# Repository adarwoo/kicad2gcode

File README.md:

# kicad2gcode

This project aims at providing a highly customisable tool to generate some GCode
for any CNC directly from a KiCAD PCB file.
It aims to be used in 3 different ways:
1. As a KiCAD plugin, so the GCode can be produced right from KiCAD
2. As a standalone command line type application for automation into other processed
3. As an API to use in a more integrated solution such as a Rasperry Pi connected to the CNC

**NOTE**: THIS IS WORK IN PROGRESS. It is activelly being developped but is not completed.

## Features

### Support for ATC and manual tool change
Define standard racks and use them.
The existing rack is evaluated and an updated version is generated along with
instructions for the changes required (add or replace a bit).

Racks are optimized to minimise the number of tool changes and are always sorted
to make the operator's life easier.
Racks can have un-usable slots too.

Get rack composition clearly layed out for you.

### Custom shop tools
Define you cutting tools on hand and let the software work it out for you.
It uses your tolerance to optimise the work.
If holes cannot be drilled (no adequate size), a router bit is used instead.
The software check the drilling depth required based on the bit diameter and
geometry and ensure it does not go through the backing board.

### Optimized machining
A Travelling Salesman Problem is applied throughout to minimise traveling time.
This is applied for drilling and routing.

### Support for different units
Versed in all unit systems, you can use the unit you prefer. This can be
used throughout the configuration. The units used are kept throughout.
Imperial can also be expressed in fractions, with the fractions kept in the display.

### Manufacturer's data
The configuration comes with manufacturing data to optimize the experience for
each cutting tool.
The software can extrapolate the manufacturing data for in-between sizes.
The generated code optimised the feed rate and spindle speed based on the
manufacturing data and the CNC capability.

## Installation
The intent is to host it on pip -that's outstanding too.
```bash
$ pip install kicad2gcode
```

## Usage

```
Usage: kicad2gcode [OPTIONS] FILENAME

  A utility which take a KiCAD v7 PCB and creates the GCode for a CNC to drill
  and route the PCB. The utility is heavily configurable. The initial set of
  configuration files is create the first time the utility runs. You can then
  edit them. The default path is ~/.kicad2gcode.

Options:
  -p, --pth              Drill and route all requiring plating.
  -n, --npth             Final drills and route and non-plated features
  -l, --outline          Route the PCB outiline
  -a, --all              Do all operations
  -o, --output FILENAME  Specify an output file name. Defaults to stdout
  --help                 Show this message and exit.
```

## Contributing

My objective is to get a working application by September 2024. This should machine
holes and outlines (pth and npth).
The outiline routing is turning out far more complex than I had anticipated, since
the output data from KiCAD are dijointed segments, requiring to re-create a closed
geometry using Eulerian Path and other graph theory. As KiCAD supports non-linear
geometry, this is made even hardware, and require some approximation.
I am using the work from https://github.com/kicad2gcode/kicad2gcode (which relies on Gerber
data) for inspiration - both making it Pythonic.
The effort is also helping the project move towards being able to engrave PCBs and
promoting an architecture which should allow for engraving. But I have no need
for engraving for now as I etch PCBs.
Let me know if you are interrested in contributing.
The tests do not provide 100% coverage yet and the code could be cleaned up too.

## License

`kicad2gcode` was created by Guillaume ARRECKX.
It is licensed under the terms of the GNU General Public License v3.0 license.

## Credits

`kicad2gcode` was created with [`cookiecutter`](https://cookiecutter.readthedocs.io/en/latest/) and the `py-pkgs-cookiecutter` [template](https://github.com/py-pkgs/py-pkgs-cookiecutter).

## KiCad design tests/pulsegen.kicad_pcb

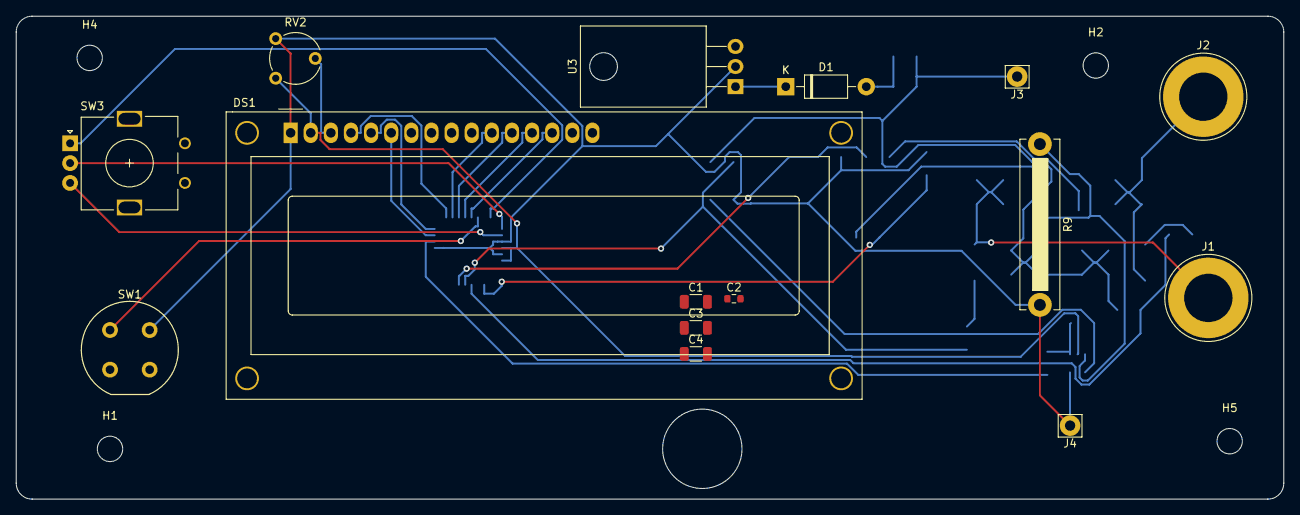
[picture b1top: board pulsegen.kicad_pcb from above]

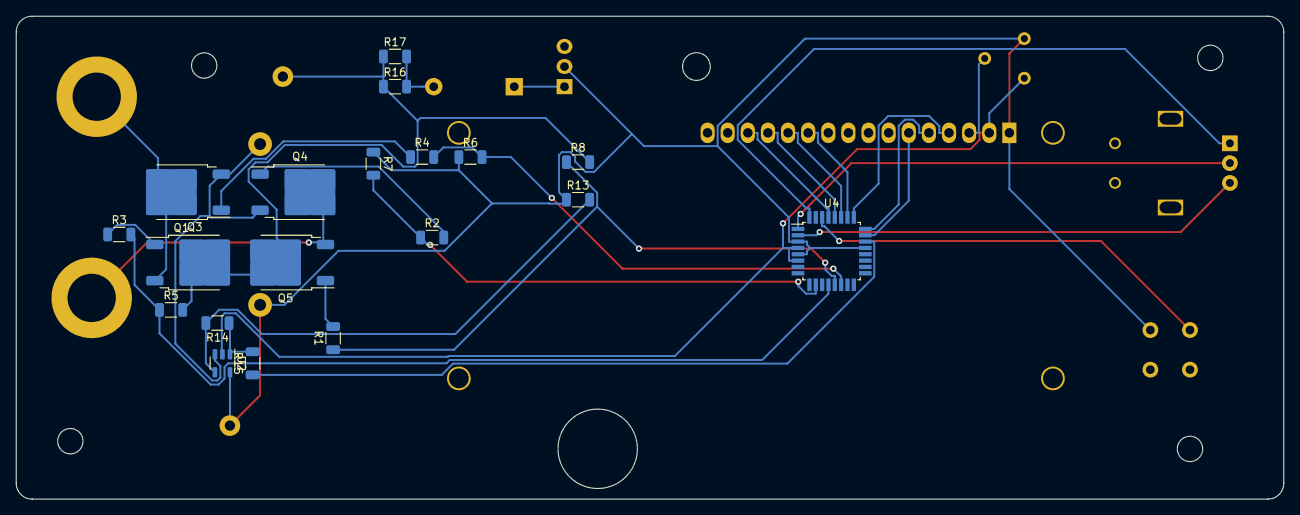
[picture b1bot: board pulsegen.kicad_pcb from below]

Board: 2 copper layers, 160.0 x 61.0 mm, 38 parts (19 on the bottom side), 32 nets.

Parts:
C1, C3, C4: 10u; R_1206_3216Metric
C2: C; R_0603_1608Metric
D1: 1N4007; D_DO-41_SOD81_P10.16mm_Horizontal
DS1: WC1602A
H1, H2, H4, H5: MountingHole; MountingHole_3.2mm_M3
J1, J2: Screw_Terminal_01x01; Banana_Jack_1Pin
J3, J4: Screw_Terminal_01x01; Pin_D1.3mm_L11.3mm_W2.8mm_Flat
Q1, Q4: QM6006D; TO-252-2
Q3, Q5: QM6015D; TO-252-2
R1, R2, R3, R4: 22; R_1206_3216Metric
R5, R6, R7, R8: 10k; R_1206_3216Metric
R9: 0.01 5W; R_Bare_Metal_Element_L21.3mm_W4.8mm_P20.30mm
R13, R15: 1k; R_1206_3216Metric
R14: 100k; R_1206_3216Metric
R16, R17: R; R_1206_3216Metric
RV2: R_Potentiometer; Potentiometer_Piher_PT-6-V_Vertical
SW1: SW_Push; Push_E-Switch_KS01Q01
SW3: RotaryEncoder_Switch; RotaryEncoder_Alps_EC11E_Vertical_H20mm
U2: MCP6001R; SOT-23-5
U3: LM7805_TO220; TO-220-3_Horizontal_TabDown
U4: ATmega328-A; TQFP-32_7x7mm_P0.8mm

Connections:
/LCD.D4: DS1.11 (D4), U4.26 (PC3)
/LCD.D5: DS1.12 (D5), U4.27 (PC4)
/LCD.D6: DS1.13 (D6), U4.28 (PC5)
/LCD.D7: DS1.14 (D7), U4.29 (~RESET/PC6)
/LCD.E: DS1.6 (E), U4.23 (PC0)
/LCD.RS: DS1.4 (RS), U4.25 (PC2)
/LCD.R/~W: DS1.5 (R/W), U4.24 (PC1)
GND: C1.2, C2.2, C3.2, C4.2, DS1.1 (VSS), J4.1, R6.1, R7.1, R9.2, R13.1, RV2.3, SW1.2, U2.5 (V-), U3.2 (GND), U4.3 (GND), U4.5 (GND), U4.21 (GND)
Ismooth: C1.1, R15.1, U4.22 (ADC7)
unnamed: D1.2 (A), R16.2, R17.2
unnamed: C4.1, D1.1 (K), U3.1 (VI)
unnamed: DS1.3 (VO), RV2.2
unnamed: J1.1, Q4.2 (D), Q5.3 (S)
unnamed: J2.1, Q1.2 (D), Q3.3 (S)
unnamed: Q1.1 (G), R4.1
unnamed: Q1.3 (S), Q4.3 (S), R9.1, U2.3 (+)
unnamed: Q3.1 (G), R3.1
unnamed: Q4.1 (G), R2.2
unnamed: Q5.1 (G), R1.2
unnamed: R14.1, R15.2, U2.1
unnamed: R13.2, R14.2, U2.4 (-)
unnamed: C3.1, U3.3 (VO)
unnamed: R3.2, R5.1, U4.12 (PB0)
unnamed: R1.1, R8.1, U4.13 (PB1)
unnamed: R4.2, R6.2, U4.14 (PB2)
unnamed: SW1.1, U4.30 (PD0)
unnamed: SW3.A, U4.32 (PD2)
unnamed: SW3.C, U4.1 (PD3)
unnamed: SW3.B, U4.2 (PD4)
unnamed: R2.1, R7.2, U4.10 (PD6)
VCC: C2.1, DS1.2 (VDD), RV2.1, U2.2 (V+), U4.4 (VCC), U4.6 (VCC)
VDD: J3.1, Q3.2 (D), Q5.2 (D), R5.2, R8.2, R16.1, R17.1

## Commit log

2023-08-11 Initial release. Moving out of KiCad
2023-08-11 Adding test files
2023-08-12 Reorg
2023-08-14 Adding notes and started reworking the file names
2023-08-16 Still working on it
2023-08-16 Thanks chatgpt for speeding that up - although - I had to make it work for real...
2023-08-17 Using a src structure
2023-08-17 Used poetry now
2023-08-17 Still faffing
2023-08-17 Switching to all YAML!
2023-08-18 New schemas
2023-08-18 Still working on the config
2023-08-19 Started testing confg
2023-08-20 Starts to run
2023-08-22 Trying to get the schema to work
2023-08-24 Bug to work out
2023-08-27 Cant get comments to work
2023-08-27 Comments are working
2023-08-28 Tests are comming together
2023-08-29 Looking into tests
2023-08-29 test: 1st test to pass. One of many to come
2023-08-30 Changing python version to see the effect on CI
2023-08-30 Debugging pytest in CI
2023-08-30 Testing ci
2023-08-30 Renaming all to pcbgcode as this could be the issue with the ci not working. Pep8 is not so clear about naming...
2023-08-30 Revert "Renaming all to pcbgcode as this could be the issue with the ci not working. Pep8 is not so clear about naming..."
    This reverts commit 7816b01a2620eebd730a9a2e6bda5f3f7c2b8fcb.
2023-08-30 Undid the renaming - but added __init__.py in tests... some post seems to indicated this is required...
2023-08-30 Moved the modules down
2023-08-30 No docs for now
2023-08-30 Update of the actions
2023-08-31 Added UT for units
2023-08-31 test: Units has 99% coverage
2023-09-01 New operators for unit. Clean up of cutting_tools and cutting tools test
2023-09-01 Moved getting a normal bit size into the cutting tools realm
2023-09-02 Added test for the request
2023-09-02 Added rack test
2023-09-06 Almost there. Cli to be tested and processor to complete
2023-09-07 Trying to get it to work in windows.
2023-09-07 More tweaks and initial machining test ok
2023-09-08 TSP is added and vectors for routing too.
2023-09-08 Command line is ok. Code structure is almost complete.
2023-09-08 Command line is starting to work and tests are ok. TSP is done too. GCode to generate now
2023-09-08 Make things clear
2023-09-08 Remove unused files
2023-09-09 Adding copyright notice
2023-09-09 Added GPL headers and started cleaning the code
2023-09-09 Fixing pep and lint issues
2023-09-09 Report warnings about tools only once
2023-09-09 Cleanup still on progress
2023-09-10 First clean gcode is generated with drills and routed holes
2023-09-10 Tried this library for meta programming of the gcode - but ended up with straight python
2023-09-11 Added limits for all feedrates. Passing a context object
2023-09-11 Fixed tool change
2023-09-11 Added rounding all round
2023-09-11 Fixed test where the config limit kicks in
2023-09-11 Trying to fix kicad screen coordinates
2023-09-12 Fixed the generated gcode
2023-09-12 Fixed generated GCode
2023-09-12 Added collection of segments from KiCAD for the contour
2023-10-10 Update README.md
    Change the project name to avoid confusion
2023-10-11 Renamed the project to avoid confusion with the existing
2023-10-11 Renaming of the project
2023-10-12 Fixed the config merge
2023-10-13 Rebuilt pcbnew for test
2023-10-13 Removed pcbnew
2023-10-13 Using links for the pcbnew
2023-10-13 Putting the pcbnew back as link
2023-10-13 Putting the pcbnew back
2023-10-13 Fixed default case in config
2023-11-04 Renaming to k2g
2024-03-21 Change release date
